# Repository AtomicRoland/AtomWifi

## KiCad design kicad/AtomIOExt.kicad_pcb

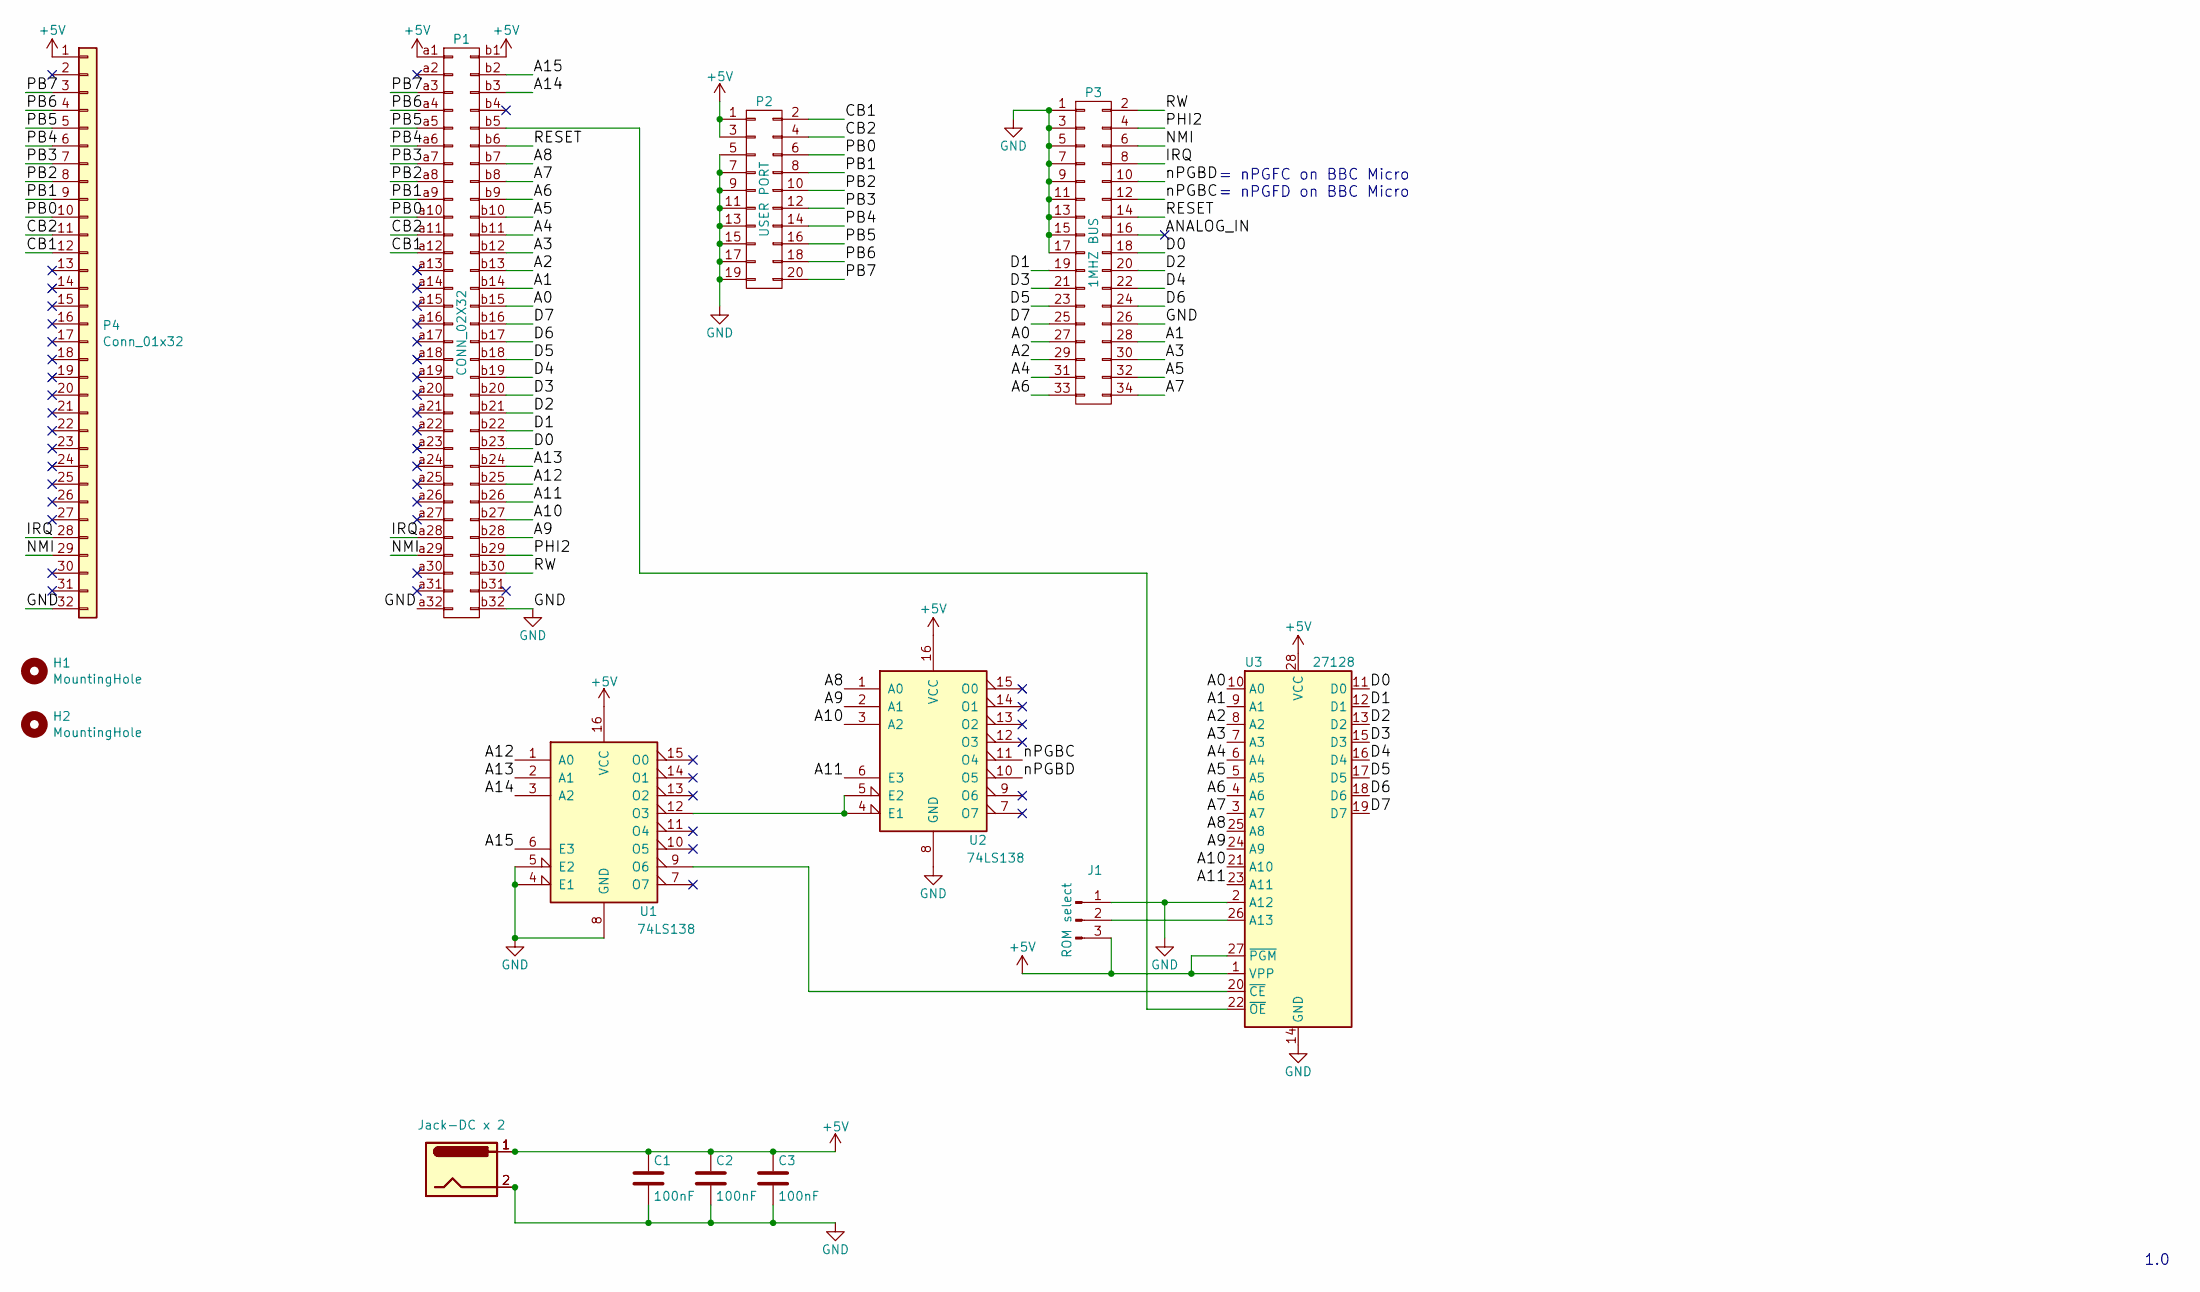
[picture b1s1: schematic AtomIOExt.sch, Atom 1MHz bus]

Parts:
C1, C2, C3: 100nF; C_Disc_D5.0mm_W2.5mm_P5.00mm
H1, H2: MountingHole; MountingHole_4.3mm_M4
J1: ROM select; PinHeader_1x03_P2.54mm_Vertical
J9: Jack-DC x 2; BarrelJack_Horizontal
J10: Jack-DC; BarrelJack_Horizontal
P1: CONN_02X32; DIN41612_B_2x32_Horizontal
P2: USER PORT; IDC-Header_2x10_P2.54mm_Vertical
P3: 1MHZ BUS; IDC-Header_2x17_P2.54mm_Vertical
P4: Conn_01x32; PinHeader_1x32_P2.54mm_Vertical
U1, U2: 74LS138; DIP-16_W7.62mm_Socket_LongPads
U3: 27128; DIP-28_W15.24mm

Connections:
+5V: C1.1, C2.1, C3.1, J1.3, J9.1, J10.1, P1.a1, P1.b1, P2.1, P2.3, P4.1, U1.16 (VCC), U2.16 (VCC), U3.1 (VPP), U3.27 (~PGM), U3.28 (VCC)
/A0: P1.b15, P3.27, U3.10 (A0)
/A1: P1.b14, P3.28, U3.9 (A1)
/A2: P1.b13, P3.29, U3.8 (A2)
/A3: P1.b12, P3.30, U3.7 (A3)
/A4: P1.b11, P3.31, U3.6 (A4)
/A5: P1.b10, P3.32, U3.5 (A5)
/A6: P1.b9, P3.33, U3.4 (A6)
/A7: P1.b8, P3.34, U3.3 (A7)
/A8: P1.b7, U2.1 (A0), U3.25 (A8)
/A9: P1.b28, U2.2 (A1), U3.24 (A9)
/A10: P1.b27, U2.3 (A2), U3.21 (A10)
/A11: P1.b26, U2.6 (E3), U3.23 (A11)
/A12: P1.b25, U1.1 (A0)
/A13: P1.b24, U1.2 (A1)
/A14: P1.b3, U1.3 (A2)
/A15: P1.b2, U1.6 (E3)
/CB1: P1.a12, P2.2, P4.12
/CB2: P1.a11, P2.4, P4.11
/D0: P1.b23, P3.18, U3.11 (D0)
/D1: P1.b22, P3.19, U3.12 (D1)
/D2: P1.b21, P3.20, U3.13 (D2)
/D3: P1.b20, P3.21, U3.15 (D3)
/D4: P1.b19, P3.22, U3.16 (D4)
/D5: P1.b18, P3.23, U3.17 (D5)
/D6: P1.b17, P3.24, U3.18 (D6)
/D7: P1.b16, P3.25, U3.19 (D7)
/IRQ: P1.a28, P3.8, P4.28
/NMI: P1.a29, P3.6, P4.29
/PB0: P1.a10, P2.6, P4.10
/PB1: P1.a9, P2.8, P4.9
/PB2: P1.a8, P2.10, P4.8
/PB3: P1.a7, P2.12, P4.7
/PB4: P1.a6, P2.14, P4.6
/PB5: P1.a5, P2.16, P4.5
/PB6: P1.a4, P2.18, P4.4
/PB7: P1.a3, P2.20, P4.3
/PHI2: P1.b29, P3.4
/RESET: P1.b6, P3.14
/RW: P1.b30, P3.2
/nPGBC: P3.12, U2.11 (O4)
/nPGBD: P3.10, U2.10 (O5)
GND: C1.2, C2.2, C3.2, J1.1, J9.2, J10.2, P1.a32, P1.b32, P2.5, P2.7, P2.9, P2.11, P2.13, P2.15, P2.17, P2.19, P3.1, P3.3, P3.5, P3.7, P3.9, P3.11, P3.13, P3.15, P3.17, P3.26, P4.32, U1.4 (E1), U1.5 (E2), U1.8 (GND), U2.8 (GND), U3.2 (A12), U3.14 (GND)
unnamed: J1.2, U3.26 (A13)
unnamed: P1.b5, U3.22 (~OE)
unnamed: U1.9 (O6), U3.20 (~CE)
unnamed: U1.12 (O3), U2.4 (E1), U2.5 (E2)

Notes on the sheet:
1.0
= nPGFC on BBC Micro = nPGFD on BBC Micro

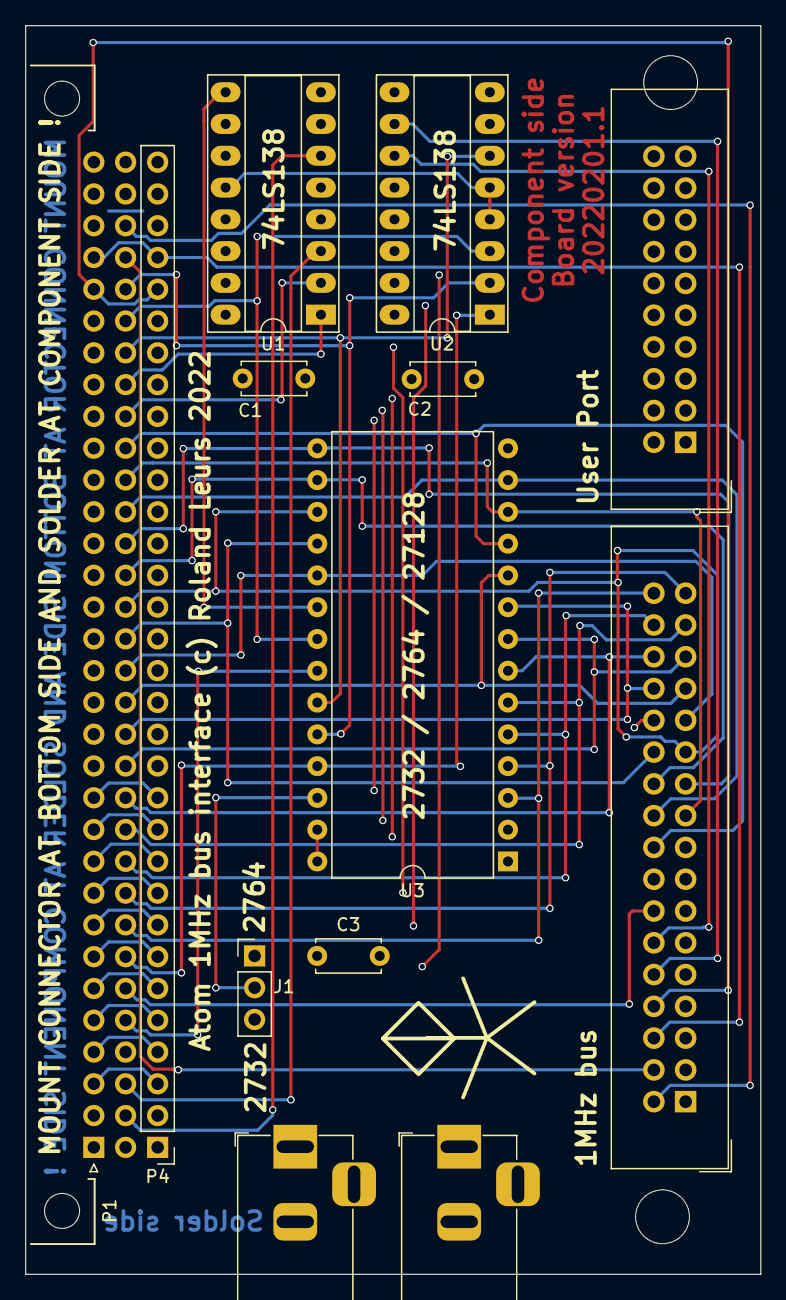
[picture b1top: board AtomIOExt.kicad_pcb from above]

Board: 4 copper layers, 58.8 x 99.8 mm, 15 parts (0 on the bottom side), 47 nets.

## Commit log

2024-08-25 Added: Wifi commands for Acorn Atom Wifi commands for Acorn System 5
